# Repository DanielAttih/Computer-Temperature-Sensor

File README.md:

# Computer-Temperature-Sensor

Reads the internal air temperature of a PC case and displays the value on an OLED. LEDs give visual status feedback.

**Status:** Firmware complete and tested on a Nucleo-L432KC dev board. Schematic complete (KiCad, ERC clean). PCB layout v2 complete (no DRC errors, schematic parity clean), with Gerber and drill files in `hardware/gerbers/`. Ordering boards from JLCPCB is next, followed by assembly and bring-up. The first layout, as originally posted, is tagged `v1.0-linkedin`; v2 swaps the OLED's male header for a female socket and rearranges the placement.

---

## Overview

This project is a custom PCB built around an STM32 microcontroller. The system measures the air temperature inside a PC case and displays it in real time (in both °C and °F) on an OLED screen. It also provides visual status using LEDs, including fault indication if the sensor or display fails.

The project follows a strict sequential methodology: documentation → prototyping on a dev board → schematic → PCB layout → firmware flashing on the final board.

---

## System Behavior

1. The temperature sensor measures the **air inside the PC case**.
2. The board is powered via **USB (5V)** from the PC.
3. The board regulates 5V down to **3.3V**.
4. The STM32 reads temperature over **I2C**.
5. The OLED displays the temperature continuously in °C and °F.
6. LEDs provide visual feedback (normal vs hot, plus fault indication).

---

## Architecture

```
USB 5V → LDO → 3.3V rail

STM32 ↔ I2C3 ↔ MCP9808 (Temp Sensor)
STM32 ↔ I2C1 ↔ SSD1306 (OLED)

STM32 → LEDs (status)
STM32 ↔ SWD (program/debug)
```

The sensor and the OLED are on **two separate I2C buses**, each with its own pull-up resistors. This matches the firmware that was tested on the dev board.

---

## Parts

### Microcontroller (MCU)

**STM32L432KCU6** (UFQFPN-32 package)
- Cortex-M4 @ up to 80 MHz (this firmware runs it at 32 MHz from the internal MSI oscillator)
- 256 KB Flash / 64 KB RAM
- Operates at 1.7–3.6 V
- UFQFPN-32 package (5×5 mm, 32-pin)

Design choices:
- Using the **bare IC (not a development board)**
- Prototyping used the "STM32 Nucleo-32 Development Board with STM32L432KC MCU" (Nucleo-L432KC)
- **No external crystals.** Both HSE and LSE are disabled; the internal MSI oscillator drives the PLL

Link(s):
- https://www.st.com/en/microcontrollers-microprocessors/stm32l432kc.html#overview
- https://www.tme.com/il/en/details/nucleo-l432kc/stm-development-kits/stmicroelectronics/

---

### Temperature Sensor

**MCP9808 (Bare IC - 8-MSOP)**

- Digital I2C temperature sensor
- High accuracy (±0.25°C)
- High resolution (0.0625°C)
- Operates at 3.3V
- I2C address 0x18 (7-bit)

Design choices:
- Using **bare IC (not breakout)**
- Prototyping used the MCP9808 Breakout Board from Adafruit
- Placed **at PCB edge** for accurate air measurement
- Includes **0.1 µF decoupling capacitor**
- Address pins (A0, A1, A2) tied to GND
- ALERT pin left unconnected (no-connect flag in the schematic)

Link(s):
- Breakout Board: https://www.adafruit.com/product/1782
- https://ww1.microchip.com/downloads/en/DeviceDoc/25095A.pdf
- https://www.digikey.com/en/products/detail/microchip-technology/MCP9808-E-MS/2802083

---

### OLED Display

**SSD1306 OLED (0.96", 128×64, I2C)**

- Rectangular display
- Good resolution for text
- Very common and well-supported
- Uses I2C, address 0x3C (7-bit)

Design choices:
- Using **module (not bare display)**
- Connected via a **1×4 female socket (2.54 mm)**: the module comes with male header pins soldered on, and they plug into the socket
- On its **own I2C bus** (I2C1), separate from the sensor
- 4.7 µF capacitor (C11) from 3.3V to GND at the header's power pin, for the display's pulsed current
- The module has its own pull-ups (measured roughly 11–12 kΩ on SDA and 19–20 kΩ on SCL, in circuit). The board still has its own 4.7 kΩ pull-ups on this bus; the two sets sit in parallel. Mark them DNP if the module's pull-ups are later confirmed sufficient.

Pinout (matches the printed order on the module):
1. GND
2. 3.3V
3. SCL
4. SDA

Link:
https://www.amazon.com/UCTRONICS-SSD1306-Self-Luminous-Display-Raspberry/dp/B072Q2X2LL

---

### LEDs

Normal operation:
- **Green LED solid** → normal temperature
- **Red LED solid** → high temperature
- **Blue LED solid** → OLED initialized and working

Fault indication:
- **Red LED flashing** → MCP9808 initialization failed (startup) or sensor stopped responding (during operation)
- **Blue LED flashing** → OLED initialization failed

Design:
- SMD 0805 LEDs
- Each LED has a **220 Ω** series resistor (same value as used on the breadboard prototype)
- Estimated current at 3.3V: roughly 5–6 mA for red and green, roughly 1–2 mA for blue (blue LEDs have a higher forward voltage, so it will be dimmer; actual values depend on the LED part chosen)
- Status LEDs are driven directly by STM32 GPIO pins

Link(s):
https://www.digikey.com/en/products/filter/led-indication-discrete/0805/105?s=N4IgjCBcpgTAnBaIDGUBmBDANgZwKYA0IAbgHZQAuATgK5EgD2UA2iAMzzuwAcIAusQAOlKCADKNAJZkA5iAC%2BSoA

---

### Programming & Debugging

**5-pin SWD Header (1×5, 2.54 mm)**

Pinout:
1. 3.3V
2. SWDIO
3. GND
4. SWCLK
5. NRST

- Standard STM32 debug interface
- Reliable and simple
- Flashing and debugging use an external ST-LINK probe connected to this header
- Pin 1 (3.3V) is a voltage reference tied to the board's 3.3V rail. On many ST-LINK V2 clones this pin is an output, so leave that wire disconnected when the board is already powered over USB.

---

### Debug UART Header

**2-pin header (1×2, 2.54 mm)**

Pinout:
1. TX (PA2, USART2_TX)
2. GND

- Connect a 3.3V USB-serial adapter to view debug messages in a terminal (115200 baud, 8N1), as was done with PuTTY on the Nucleo
- Transmit only (RX is not used)
- Used for bring-up and fault messages (for example sensor and OLED init status)

---

### Power System

#### Input

**Micro-USB (Type-B): Amphenol 10118194-0001LF**
- Used for **power only**
- Provides 5V

Connections:
- VBUS → 5V rail
- GND and shield → GND
- D+ / D- / ID → NC (no-connect flags in the schematic)

Link(s):
- https://www.amphenol-cs.com/product/101181940001lf.html
- https://www.digikey.com/en/products/detail/amphenol-cs-fci/10118194-0001LF/2785389

---

#### Voltage Regulator

**AP2112K-3.3TRG1 (LDO)**

- Output: 3.3V
- Max current: 600 mA
- EN pin tied to VIN (regulator always enabled)

Capacitors:
- CIN = 1 µF (C8, input, on 5V rail side)
- COUT = 1 µF (C9, output, on 3.3V rail side)
- CBULK = 10 µF, 16 V (C7, on 5V rail, before LDO, for USB inrush)

Link(s):
- https://www.digikey.com/en/products/detail/diodes-incorporated/AP2112K-3-3TRG1/4470746
- https://www.mouser.com/ProductDetail/Diodes-Incorporated/AP2112K-3.3TRG1?qs=x6A8l6qLYDDPYHosCdzh%2FA%3D%3D&srsltid=AfmBOop9CtVNQ4PzkGa5PHwTKG7HFoA91sVGvN81iwmOFJOXiIA_Ls7D

---

### Power Distribution

5V → LDO → 3.3V rail

3.3V powers:
- STM32
- MCP9808
- OLED
- LEDs
- SWD reference

---

### Power Budget

Approximate worst-case figures:

| Component | Current |
|---|---|
| STM32L432 active | ~10 mA |
| SSD1306 OLED | ~20 mA |
| MCP9808 | ~0.4 mA |
| 3 × LEDs (220 Ω: ~5.5 + ~5.5 + ~1.4 mA) | ~12 mA |
| **Total** | **~43 mA** |

Well within the AP2112K's 600 mA rating. (Red and green are never on together in normal operation, so real draw is usually lower.)

---

## Supporting Components

### STM32 Decoupling
- One 0.1 µF cap per VDD pin (C1 on pin 1, C2 on pin 17), placed as close to each pin as possible
- One 0.1 µF cap (C3) on VDDA (pin 5), plus 1 µF (C4) on VDDA
- 4.7 µF bulk capacitor (C5) on the 3.3V rail near the MCU
- The exposed pad (pin 33) and VSS pins 16 and 32 all go to GND

Note: VDDA must be powered and decoupled even if ADC/DAC are not used.

Part: Generic 0402 or 0603 MLCC, 0.1 µF / 10V / X5R or better

---

### I2C Buses

Two independent buses, one device each:

| Bus | Device | Address (7-bit) | SDA | SCL |
|---|---|---|---|---|
| I2C1 | SSD1306 OLED | 0x3C | PB7 | PB6 |
| I2C3 | MCP9808 | 0x18 | PB4 | PA7 |

Pull-ups (one pair per bus, 4.7 kΩ to 3.3V):
- I2C3 (MCP9808): R2 on SDA, R3 on SCL
- I2C1 (OLED): R4 on SDA, R5 on SCL

Note: the OLED module has its own pull-ups (see OLED Display above), so the I2C1 pair is in parallel with them. The MCP9808 is a bare IC, so its pull-ups are the only ones on I2C3.

Net names in the schematic: `I2C1_SDA`, `I2C1_SCL`, `I2C3_SDA`, `I2C3_SCL`.

---

### Reset Circuit

Pushbutton: Panasonic EVQ-PUJ02K (or equivalent SMD 3 × 4 mm)

- This is a **side-operated** switch: the actuator is pressed horizontally, from the side it faces. On the board it sits on the left edge with the actuator facing outward and overhanging the edge by about 0.4 mm, so it can be reached through a cutout in the case.

- NRST → pushbutton → GND
- 100 nF capacitor (C6) from NRST to GND, for noise immunity and button debounce
- No external pull-up needed (NRST has an internal pull-up)
- NRST also goes to SWD header pin 5 so the probe can reset the MCU

Link(s):
https://www.digikey.com/en/products/detail/panasonic-electronic-components/EVQ-PUJ02K/286348

---

### Boot Configuration

**BOOT0 pull-down resistor: 10 kΩ (0402 or 0603)**

- BOOT0 (pin 31, labeled PH3 on the symbol) → 10 kΩ (R1) → GND
- Keeps STM32 in normal flash boot mode
- Programming is over SWD only (USB is power-only), so no bootloader jumper

Part: Generic 0402 or 0603 thick film resistor 10 kΩ

---

### Test Points

Added for debugging (2 mm pads, TP1 to TP6):
- 3.3V
- GND
- I2C1 SDA and SCL (OLED bus)
- I2C3 SDA and SCL (sensor bus)

---

## Schematic Reference Designators

| Ref | Part | Value / note |
|---|---|---|
| U1 | STM32L432KCU6 | MCU |
| U2 | AP2112K-3.3 | 3.3V LDO |
| U3 | MCP9808 (MSOP-8) | Temperature sensor |
| J_USB | Micro-USB (Amphenol 10118194-0001LF) | Power only |
| J_SWD | 1×5 header | SWD |
| J_SSD1306 | 1×4 female socket | OLED module (plugs onto the module's header pins) |
| J_UART | 1×2 header | Debug TX + GND |
| SW1 | Panasonic EVQ-PUJ series pushbutton | Reset |
| D1, D2, D3 | 0805 LEDs | Green (PA3), red (PA4), blue (PA1) |
| R1 | 10 kΩ | BOOT0 pull-down |
| R2, R3 | 4.7 kΩ | I2C3 SDA, SCL pull-ups |
| R4, R5 | 4.7 kΩ | I2C1 SDA, SCL pull-ups |
| R6, R7, R8 | 220 Ω | Green, red, blue LED series resistors |
| C1, C2, C3 | 100 nF | MCU VDD (×2) and VDDA decoupling |
| C4 | 1 µF | VDDA |
| C5 | 4.7 µF | 3.3V bulk near MCU |
| C6 | 100 nF | NRST |
| C7 | 10 µF, 16 V | 5V bulk |
| C8 | 1 µF | LDO input |
| C9 | 1 µF | LDO output |
| C10 | 100 nF | MCP9808 decoupling |
| C11 | 4.7 µF | OLED header supply |
| TP1 to TP6 | 2 mm test pads | 3.3V, GND, I2C1 SDA/SCL, I2C3 SDA/SCL |

---

## PCB Design Choices

- 2-layer PCB
- Top layer: components + signals
- Bottom layer: ground plane (with a few short signal routes)
- Board size: 51 mm × 50.5 mm
- Shape: rectangular
- 4 × M3 mounting holes (3.2 mm), one near each corner
- USB connector (lower left) and reset button on the left edge, MCP9808 on the right edge (away from the LDO and OLED heat), OLED socket at the top edge, debug UART header at the top left, LEDs along the bottom, SWD header on the right side
- The OLED module (27 × 27 mm) plugs into its socket and lies flat above the board. The SWD header is placed outside the module's footprint, so a programmer can be connected with the display installed. The case is planned around the OLED and LEDs, leaving the sensor exposed to the PC case air
- Component reference designators in silkscreen (no board version text, header pin labels or mounting-hole labels in v2; pin 1 of each header is marked by its square pad, and the pin order is documented above)
- Fabrication files for JLCPCB (Gerbers and drill files) are in `hardware/gerbers/`

---

## Pin Assignments

Defined in STM32CubeMX and tested on the Nucleo-L432KC. Matches the final schematic (ERC clean, 2026-10-23).

| Function | MCU pin | Package pin | Peripheral / Mode | Schematic net |
|---|---|---|---|---|
| OLED SDA | PB7 | 30 | I2C1_SDA | `I2C1_SDA` |
| OLED SCL | PB6 | 29 | I2C1_SCL | `I2C1_SCL` |
| MCP9808 SDA | PB4 | 27 | I2C3_SDA | `I2C3_SDA` |
| MCP9808 SCL | PA7 | 13 | I2C3_SCL | `I2C3_SCL` |
| Green LED | PA3 | 9 | GPIO output | `LED_GREEN` |
| Red LED | PA4 | 10 | GPIO output | `LED_RED` |
| Blue LED | PA1 | 7 | GPIO output | `LED_BLUE` |
| Debug UART TX | PA2 | 8 | USART2_TX (to debug header) | `UART_TX` |
| SWDIO | PA13 | 23 | SWD | direct to header pin 2 |
| SWCLK | PA14 | 24 | SWD | direct to header pin 4 |
| NRST | NRST | 4 | Reset | `NRST` |
| BOOT0 | PH3-BOOT0 | 31 | Boot | Pulled to GND (R1) |

All other MCU pins are unused and marked no-connect.

On the Nucleo-L432KC, USART2 TX (PA2) reaches the PC through the board's ST-LINK virtual COM port. On the custom PCB it goes to the debug UART header and needs a USB-serial adapter.

---

## Firmware

Written in C with STM32CubeMX / HAL, developed in STM32CubeIDE.

### Behavior

- **Startup:** retries the MCP9808 until it answers (red LED flashes after the first few failed attempts). Tries the OLED up to 3 times, then continues without a display if it fails (blue LED flashes).
- **Main loop (every 500 ms):** reads the temperature, shows °C and °F on the OLED, and updates the red/green LEDs.
- **Temperature thresholds (with hysteresis):** red LED turns **on at 90 °F or above** and turns **off only below 85 °F**. Between 85 and 90 °F the LEDs keep their previous state, so the LED does not flicker near the threshold.
- **Sensor fault during operation:** after 3 failed reads in a row, the OLED shows `SENSOR ERR`, the green LED turns off, and the red LED flashes. The I2C peripheral is reset on failed reads, and the system recovers automatically when the sensor responds again.

| Situation | Result |
|---|---|
| Sensor missing at boot | Retries forever, red LED flashes, recovers if reconnected |
| OLED missing at boot | Continues without display, blue LED flashes, LEDs and temperature logic still work |
| Sensor lost while running | `SENSOR ERR` on OLED, red LED flashing, recovers on reconnect |

### Source files

| File | Purpose |
|---|---|
| `MCP9808.c` / `MCP9808.h` | MCP9808 sensor driver (`MCP9808_Init`, `MCP9808_ReadTempC` returning °C and °F) |
| `ssd1306.c` / `ssd1306.h` / `fonts.h` | OLED driver, third-party (see below) |
| `main.c` | Initialization, main loop, LED logic, fault handling |

### Third-party code

The SSD1306 OLED driver (`ssd1306.c`, `ssd1306.h`, and the font files) was provided in an embedded systems course. It is based on work by Tilen Majerle and Alexander Lutsai and is licensed under the **GNU GPL v3 or later**. Its original license headers are kept in the source files.

### Dev-board note (Nucleo-L432KC)

On the Nucleo-32 board, solder bridges SB16 and SB18 connect PA5 to PB7 and PA6 to PB6. Using PA5 or PA6 as outputs interferes with the I2C1 pins (it broke OLED initialization during prototyping). This only affects the Nucleo board; the custom PCB does not have these bridges.

---

## Notes

- STM32 internal clock is used (no external crystals; HSE and LSE are both disabled)
- The OLED and the sensor are on separate I2C buses
- Sensor placement is critical for accurate readings (placed at PCB edge)
- Designed for simplicity and first-pass success
- Pin assignments were defined in STM32CubeMX during firmware development and were verified against the final schematic

---

## Functionality Flow Chart

_(to be added)_

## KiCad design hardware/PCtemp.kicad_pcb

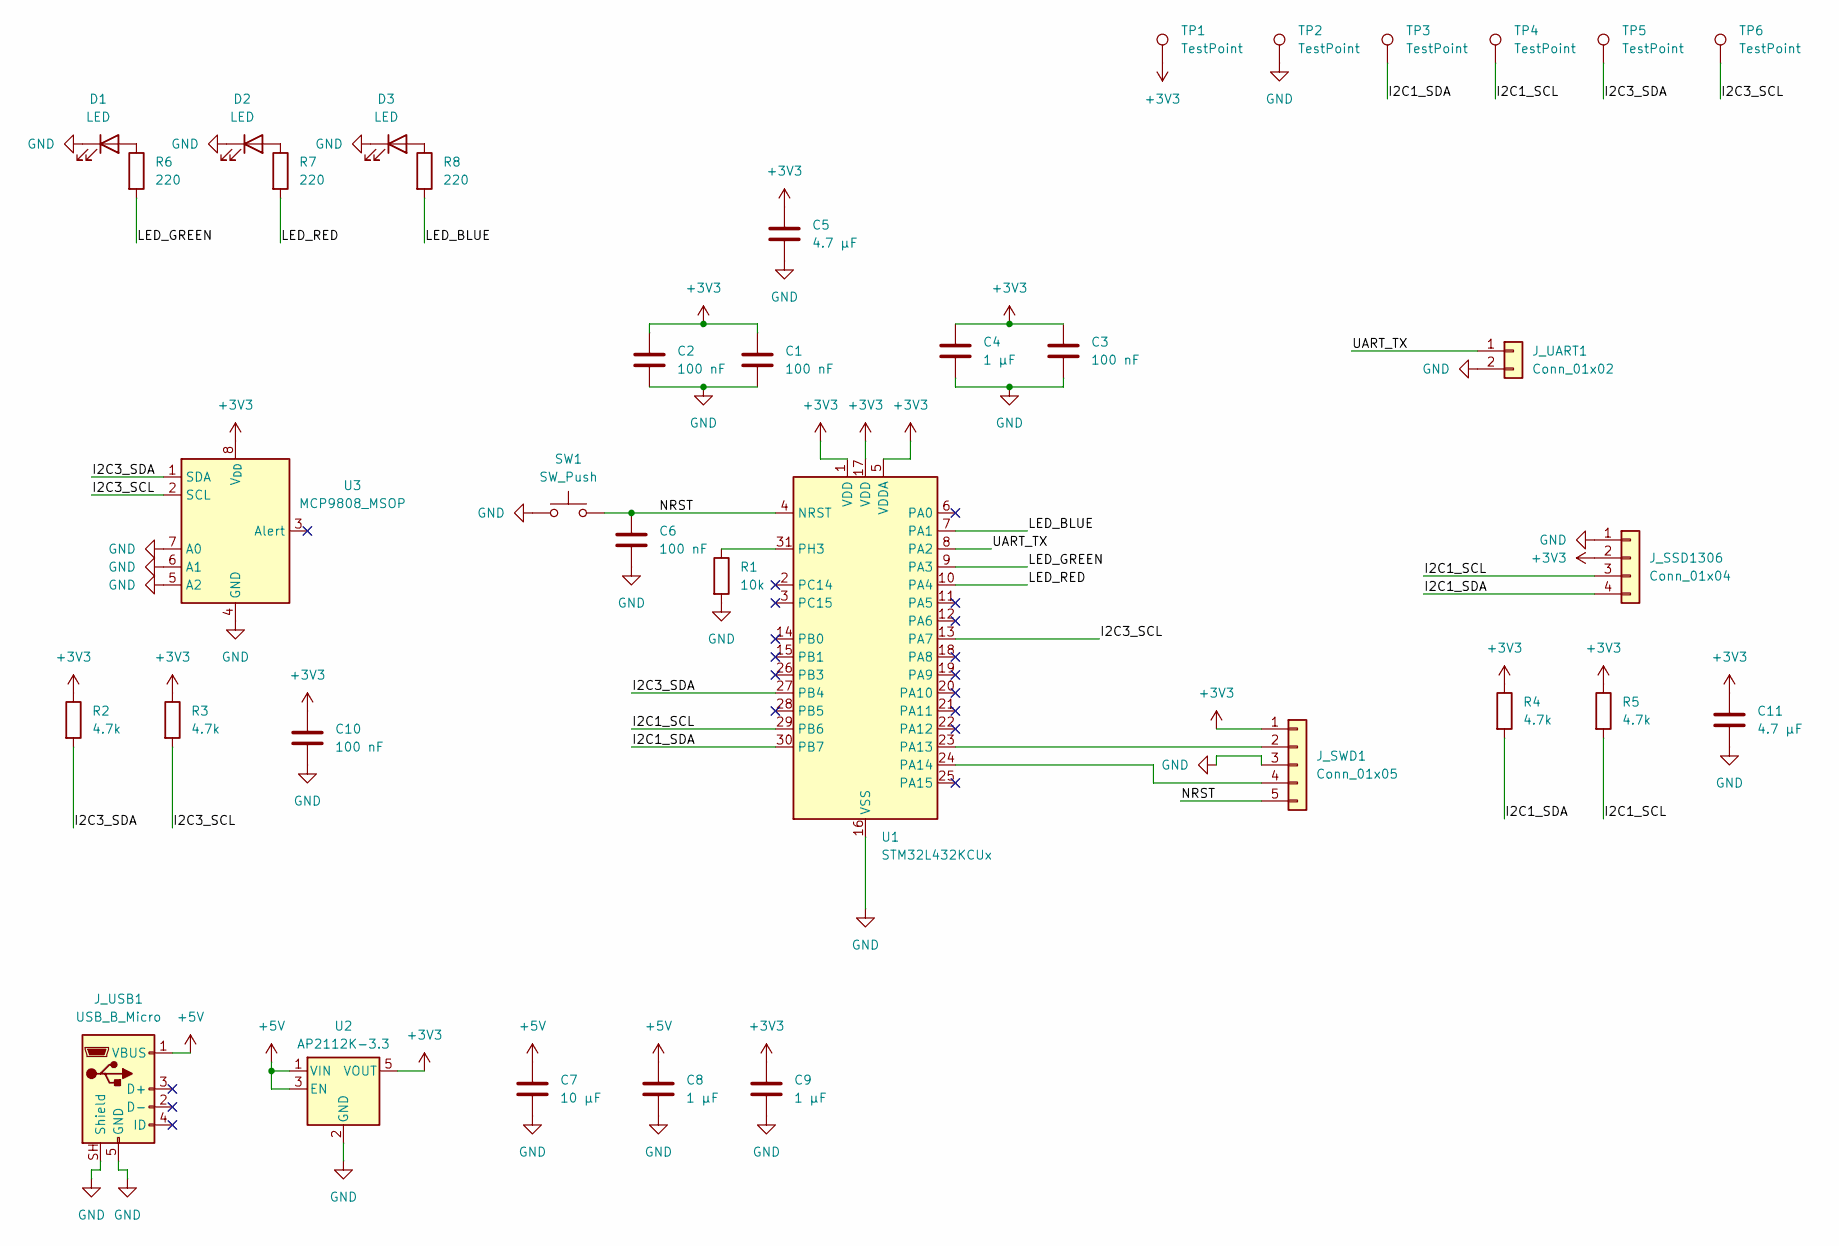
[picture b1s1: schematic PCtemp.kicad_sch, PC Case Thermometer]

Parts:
C1, C2, C3, C6, C10: 100 nF; C_0402_1005Metric
C4, C8, C9: 1 µF; C_0402_1005Metric
C5, C11: 4.7 µF; C_0603_1608Metric
C7: 10 µF; C_0603_1608Metric
D1, D2, D3: LED; LED_0805_2012Metric
J_SSD1306: Conn_01x04; PinSocket_1x04_P2.54mm_Vertical
J_SWD1: Conn_01x05; PinHeader_1x05_P2.54mm_Vertical
J_UART1: Conn_01x02; PinHeader_1x02_P2.54mm_Vertical
J_USB1: USB_B_Micro; USB_Micro-B_Amphenol_10118194_Horizontal
R1: 10k; R_0402_1005Metric
R2, R3, R4, R5: 4.7k; R_0402_1005Metric
R6, R7, R8: 220; R_0402_1005Metric
SW1: SW_Push; Panasonic_EVQPUJ_EVQPUA
TP1, TP2, TP3, TP4, TP5, TP6: TestPoint; TestPoint_Pad_D2.0mm
U1: STM32L432KCUx; QFN-32-1EP_5x5mm_P0.5mm_EP3.45x3.45mm
U2: AP2112K-3.3; SOT-23-5
U3: MCP9808_MSOP; MSOP-8_3x3mm_P0.65mm

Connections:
+3V3: C1.1, C2.1, C3.1, C4.1, C5.1, C9.1, C10.1, C11.1, J_SSD1306.2, J_SWD1.1, R2.1, R3.1, R4.1, R5.1, TP1.1 (1_1), U1.1 (VDD), U1.5 (VDDA), U1.17 (VDD), U2.5 (VOUT), U3.8 (V_{DD})
+5V: C7.1, C8.1, J_USB1.1 (VBUS), U2.1 (VIN), U2.3 (EN)
/I2C1_SCL: J_SSD1306.3, R5.2, TP4.1 (1_1), U1.29 (PB6)
/I2C1_SDA: J_SSD1306.4, R4.2, TP3.1 (1_1), U1.30 (PB7)
/I2C3_SCL: R3.2, TP6.1 (1_1), U1.13 (PA7), U3.2 (SCL)
/I2C3_SDA: R2.2, TP5.1 (1_1), U1.27 (PB4), U3.1 (SDA)
/LED_BLUE: R8.2, U1.7 (PA1)
/LED_GREEN: R6.2, U1.9 (PA3)
/LED_RED: R7.2, U1.10 (PA4)
/NRST: C6.1, J_SWD1.5, SW1.2, U1.4 (NRST)
/UART_TX: J_UART1.1, U1.8 (PA2)
GND: C1.2, C2.2, C3.2, C4.2, C5.2, C6.2, C7.2, C8.2, C9.2, C10.2, C11.2, D1.1 (K), D2.1 (K), D3.1 (K), J_SSD1306.1, J_SWD1.3, J_UART1.2, J_USB1.5 (GND), J_USB1.SH (Shield), R1.2, SW1.1, TP2.1 (1_1), U1.16 (VSS), U1.32 (VSS), U1.33 (VSS), U2.2 (GND), U3.4 (GND), U3.5 (A2), U3.6 (A1), U3.7 (A0)
unnamed: D1.2 (A), R6.1
unnamed: D2.2 (A), R7.1
unnamed: D3.2 (A), R8.1
unnamed: J_SWD1.2, U1.23 (PA13)
unnamed: J_SWD1.4, U1.24 (PA14)
unnamed: R1.1, U1.31 (PH3)

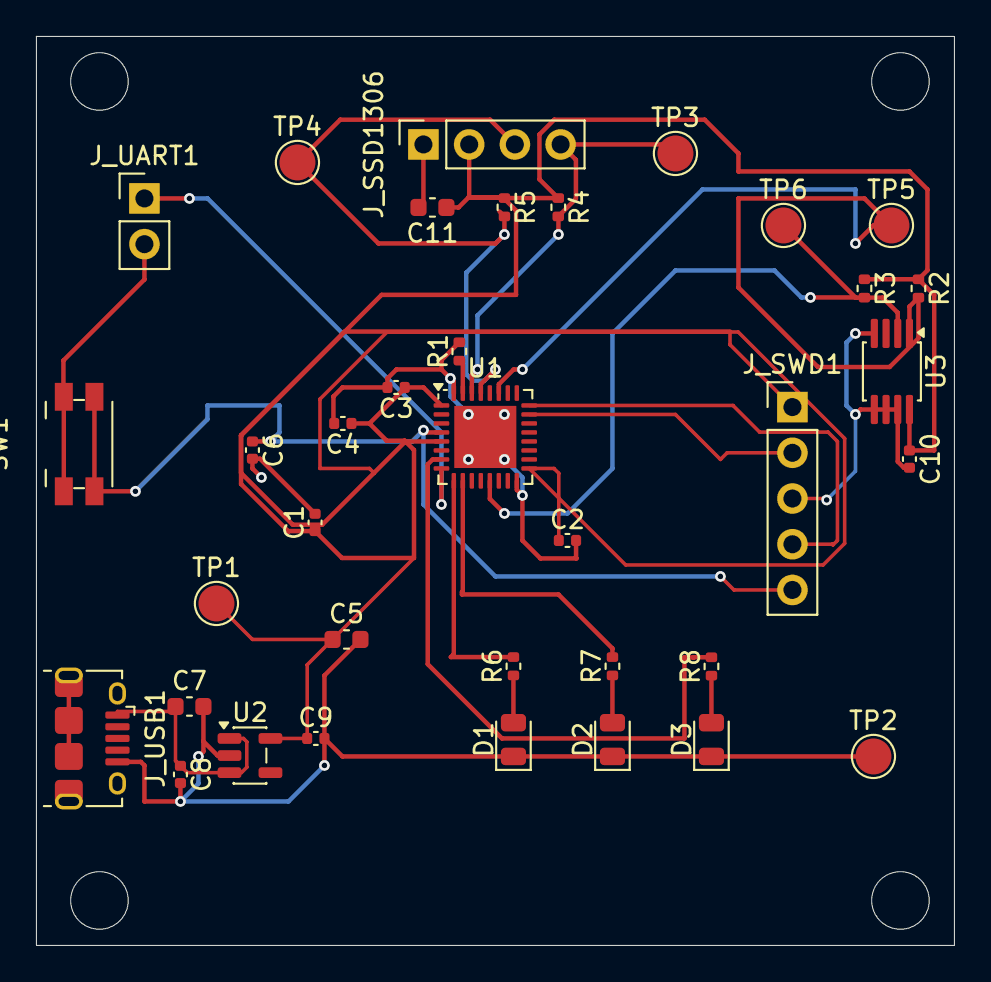
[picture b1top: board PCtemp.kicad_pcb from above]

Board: 2 copper layers, 51.0 x 50.5 mm, 40 parts (0 on the bottom side), 18 nets.

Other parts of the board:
H1, H2, H3, H4: MountingHole_3.2mm_M3

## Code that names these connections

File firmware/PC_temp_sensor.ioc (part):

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Mcu.Name=STM32L432K(B-C)Ux
Mcu.Package=UFQFPN32
Mcu.UserName=STM32L432KCUx
PA1.GPIOParameters=GPIO_Label
PA1.GPIO_Label=BLUE_LED
PA1.Signal=GPIO_Output
PA13\ (JTMS-SWDIO).GPIOParameters=GPIO_Label
PA13\ (JTMS-SWDIO).GPIO_Label=SWDIO
PA13\ (JTMS-SWDIO).Mode=Serial_Wire
PA13\ (JTMS-SWDIO).Signal=SYS_JTMS-SWDIO
PA14\ (JTCK-SWCLK).GPIOParameters=GPIO_Label
PA14\ (JTCK-SWCLK).GPIO_Label=SWCLK
PA14\ (JTCK-SWCLK).Mode=Serial_Wire
PA14\ (JTCK-SWCLK).Signal=SYS_JTCK-SWCLK
PA15\ (JTDI).Mode=Asynchronous
PA15\ (JTDI).Signal=USART2_RX
PA2.Mode=Asynchronous
PA2.Signal=USART2_TX
PA3.GPIOParameters=GPIO_Label
PA3.GPIO_Label=RED_LED
PA3.Signal=GPIO_Output
PA4.GPIOParameters=GPIO_Label
PA4.GPIO_Label=GREEN_LED
PA4.Signal=GPIO_Output
PA7.GPIOParameters=GPIO_Label
PA7.GPIO_Label=MCP9808_SCL
PA7.Mode=I2C
PA7.Signal=I2C3_SCL
PB4\ (NJTRST).GPIOParameters=GPIO_Label
PB4\ (NJTRST).GPIO_Label=MCP9808_SDA
PB4\ (NJTRST).Mode=I2C
PB4\ (NJTRST).Signal=I2C3_SDA
PB6.GPIOParameters=GPIO_Label
PB6.GPIO_Label=SSD1306_SCL
PB6.Mode=I2C
PB6.Signal=I2C1_SCL
PB7.GPIOParameters=GPIO_Label
PB7.GPIO_Label=SSD1306_SDA
PB7.Mode=I2C
PB7.Signal=I2C1_SDA
RCC.HSE_VALUE=8000000
RCC.SYSCLKFreq_VALUE=32000000
RCC.SYSCLKSource=RCC_SYSCLKSOURCE_PLLCLK
board=NUCLEO-L432KC
boardIOC=true
